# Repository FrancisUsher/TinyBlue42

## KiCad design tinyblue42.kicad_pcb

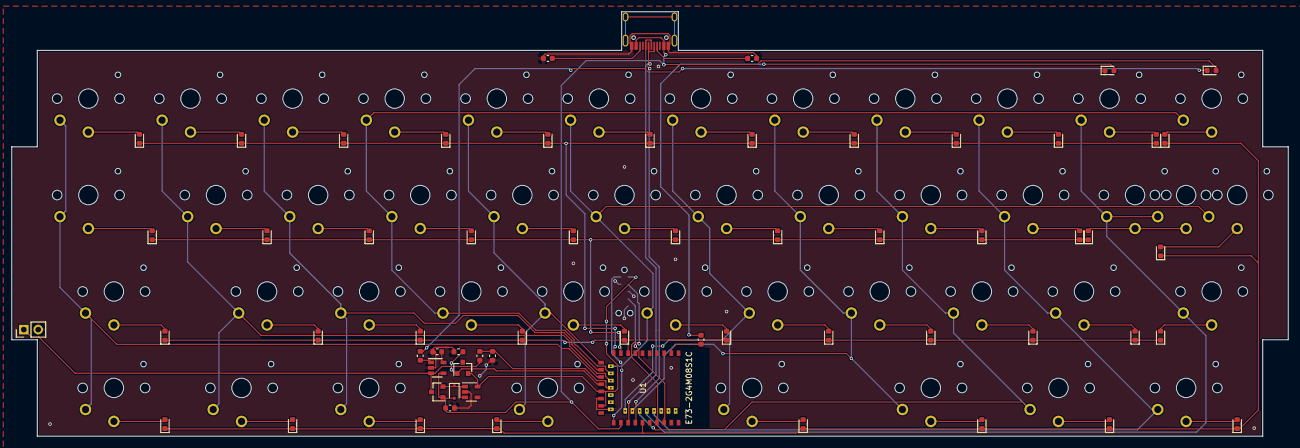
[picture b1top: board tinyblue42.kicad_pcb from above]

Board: 2 copper layers, 225.0 x 74.8 mm, 107 parts (1 on the bottom side), 77 nets.

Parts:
D1, D2, D3, D4, D5, D6, D7, D8, D9, D10, D11, D12, D13, D14, D15, D16, D17, D18, D19, D20, D21, D22, D23, D24, D25, D26, D27, D28, D29, D30, D31, D32, D33, D34, D35, D36, D37, D38, D39, D40, D41, D42, D43: CD4148W; D_0603_1608Metric
D45: BLUE; LED_0603_1608Metric
D46: RED; LED_0603_1608Metric
D47: 1N5819; D_SOD-323F
J1: Conn_01x02; PinHeader_1x02_P2.54mm_Vertical
J2: Conn_ARM_JTAG_SWD_10; Tag-Connect_TC2050-IDC-NL_2x05_P1.27mm_Vertical
Q1, Q2: AO3407; SOT-23
R1: 100K; R_0603_1608Metric
R2, R3: 5.1K; R_0603_1608Metric
R4, R8: 1K; R_0603_1608Metric
R5: 10k; R_0603_1608Metric
R6: 820K; R_0603_1608Metric
R7, R9: 2M; R_0603_1608Metric
SW1, SW2, SW3, SW4, SW5, SW6, SW7, SW8, SW9, SW10, SW11, SW12, SW13, SW14, SW15, SW16, SW17, SW18, SW19, SW20, SW21, SW22, SW23, SW24, SW25, SW26, SW27, SW28, SW29, SW30, SW31, SW32, SW33, SW34, SW35, SW36, SW37, SW38, SW39, SW40, SW41, SW42, SW43, SW45: SW_Push; SW_PG1350_choc_spacing
U1: E73-2G4M08S1C; E73-2G4M08S1C-52840
U2: XC6220B331MR-G; SOT-23-5
U3: TP4054; SOT-23-5
USB1: HRO-TYPE-C-31-M-12

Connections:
BATTERY_PIN: R6.2, R7.1, U1.18
BLUE_LED: R4.1, U1.2
CC1: R3.1, USB1.4
CC2: R2.1, USB1.10
COL0: SW1.2, SW12.2, SW23.2, SW34.2, U1.15
COL1: SW2.2, SW13.2, SW24.2, SW35.2, U1.16
COL2: SW3.2, SW14.2, SW25.2, SW36.2, U1.13
COL3: SW4.2, SW15.2, SW26.2, SW37.2, U1.14
COL4: SW5.2, SW16.2, SW27.2, SW38.2, U1.11
COL5: SW6.2, SW17.2, SW28.2, SW39.2, U1.12
COL6: SW7.2, SW18.2, SW29.2, SW40.2, U1.28
COL7: SW8.2, SW19.2, SW30.2, SW41.2, U1.30
COL8: SW9.2, SW20.2, SW31.2, SW42.2, U1.32
COL9: SW10.2, SW21.2, SW32.2, SW43.2, U1.36
COLA: SW11.2, SW22.2, SW33.2, SW45.2, U1.34
DATA+: U1.31, USB1.6, USB1.8
DATA-: U1.29, USB1.5, USB1.7
GND: D45.1, J1.2, J2.3, J2.5, J2.9, R1.2, R2.2, R3.2, R5.2, R7.2, R9.2, U1.5, U1.21, U1.24, U2.2, U3.2, USB1.1, USB1.12
unnamed: D1.2, SW1.1
unnamed: D2.2, SW2.1
unnamed: D3.2, SW3.1
unnamed: D4.2, SW4.1
unnamed: D5.2, SW5.1
unnamed: D6.2, SW6.1
unnamed: D7.2, SW7.1
unnamed: D8.2, SW8.1
unnamed: D9.2, SW9.1
unnamed: D10.2, SW10.1
unnamed: D11.2, SW11.1
unnamed: D12.2, SW12.1
unnamed: D13.2, SW13.1
unnamed: D14.2, SW14.1
unnamed: D15.2, SW15.1
unnamed: D16.2, SW16.1
unnamed: D17.2, SW17.1
unnamed: D18.2, SW18.1
unnamed: D19.2, SW19.1
unnamed: D20.2, SW20.1
unnamed: D21.2, SW21.1
unnamed: D22.2, SW22.1, SW45.1
unnamed: D23.2, SW23.1
unnamed: D24.2, SW24.1
unnamed: D25.2, SW25.1
unnamed: D26.2, SW26.1
unnamed: D27.2, SW27.1
unnamed: D28.2, SW28.1
unnamed: D29.2, SW29.1
unnamed: D30.2, SW30.1
unnamed: D31.2, SW31.1
unnamed: D32.2, SW32.1
unnamed: D33.2, SW33.1
unnamed: D34.2, SW34.1
unnamed: D35.2, SW35.1
unnamed: D36.2, SW36.1
unnamed: D37.2, SW37.1
unnamed: D38.2, SW38.1
unnamed: D39.2, SW39.1
unnamed: D40.2, SW40.1
unnamed: D41.2, SW41.1
unnamed: D42.2, SW42.1
unnamed: D43.2, SW43.1
unnamed: D45.2, R4.2
unnamed: D46.1, R8.1
unnamed: D47.1, Q1.2, U2.1, U2.3
unnamed: R5.1, U3.5
unnamed: R8.2, U3.1
POWER_PIN: Q2.1, R9.1, U1.17
RESET: J2.10, U1.26
ROW0: D1.1, D2.1, D3.1, D4.1, D5.1, D6.1, D7.1, D8.1, D9.1, D10.1, D11.1, U1.10
ROW1: D12.1, D13.1, D14.1, D15.1, D16.1, D17.1, D18.1, D19.1, D20.1, D21.1, D22.1, U1.9
ROW2: D23.1, D24.1, D25.1, D26.1, D27.1, D28.1, D29.1, D30.1, D31.1, D32.1, D33.1, U1.8
ROW3: D34.1, D35.1, D36.1, D37.1, D38.1, D39.1, D40.1, D41.1, D42.1, D43.1, U1.33
SWC: J2.4, U1.39
SWD: J2.2, U1.37
VBAT: J1.1, Q1.3, R6.1, U3.3
VBUS: D46.2, D47.2, Q1.1, R1.1, U1.27, U3.4, USB1.2, USB1.11
nRF_VDD: J2.1, Q2.2, U1.19, U1.23, U2.5

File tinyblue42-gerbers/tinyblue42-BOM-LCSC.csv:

Id,Designator,Package,Quantity,Designation,LCSC Part Number
1,U1,E73-2G4M08S1C-52840,1,E73-2G4M08S1C,C356849
3,U3,SOT-23-5,1,TP4054,C32574
4,U2,SOT-23-5,1,XC6220B331MR-G,C86534
5,"R9,R7",R_0603_1608Metric,2,2M,C22976
6,"R8,R4",R_0603_1608Metric,2,1K,C21190
7,R6,R_0603_1608Metric,1,820K,C23252
8,R5,R_0603_1608Metric,1,10k,C25804
9,"R3,R2",R_0603_1608Metric,2,5.1K,C23186
10,R1,R_0603_1608Metric,1,100K,C25803
11,"Q2,Q1",SOT-23,2,AO3407,C693136
12,D47,D_SOD-323F,1,1N5819,C440261
13,D46,LED_0603_1608Metric,1,RED,C84263
14,D45,LED_0603_1608Metric,1,BLUE,C84266
15,"D43,D42,D41,D40,D39,D38,D37,D36,D35,D34,D33,D32,D31,D30,D29,D28,D27,D26,D25,D24,D23,D22,D21,D20,D19,D18,D17,D16,D15,D14,D13,D12,D11,D10,D9,D8,D7,D6,D5,D4,D3,D2,D1",D_0603_1608Metric,43,CD4148W,C109002
17,USB1,HRO-TYPE-C-31-M-12,1,HRO-TYPE-C-31-M-12,C165948

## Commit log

2021-01-27 init
2021-01-27 docs: add empty readme
2021-03-18 chore: release under MIT license
